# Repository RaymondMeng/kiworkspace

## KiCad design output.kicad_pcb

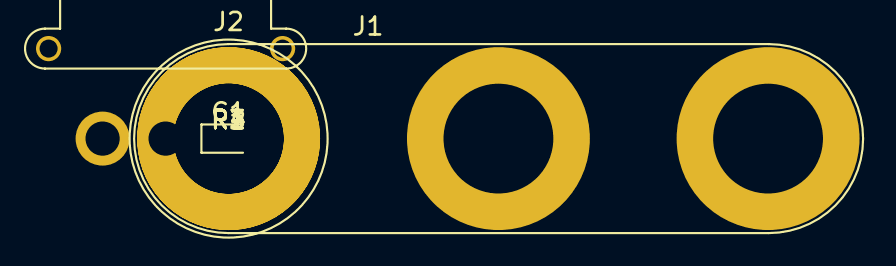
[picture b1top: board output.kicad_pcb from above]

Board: 2 copper layers, 8 parts (0 on the bottom side), 6 nets, no tracks yet.

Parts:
C1: 1uf; CP_EIA-1608-10_AVX-L
J1: Conn_01x03; Banana_Jack_3Pin
J2: Conn_01x01; Banana_Jack_1Pin
Q1: PNP; AMASS_MR30PW-FB_1x03_P3.50mm_Horizontal
R1: 10R; R_0201_0603Metric
R2: 10K; R_0201_0603Metric
R3: 1K; R_0201_0603Metric
R4: 5R; R_0201_0603Metric

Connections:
/out: J2.1, R2.1
/signal: C1.2, J1.1
GND: J1.2, Q1.3 (E), R1.2
unnamed: C1.1, Q1.2 (B), R1.1, R4.2
unnamed: Q1.1 (C), R2.2, R3.2
VCC: J1.3, R3.1, R4.1

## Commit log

2023-11-01 finish parsing of netlist's net
2023-11-02 finish basic barsing of net
2023-11-03 first_version
2023-11-03 fix some error
2023-11-04 #2 fix error: 替换正则模式为首尾匹配，解决fp_name部分缺失问题
2023-11-04 #3 fix error: 修复reference_name没有独立命名的问题
2023-11-05 #4 add & fix: 增加了pad的net内容，修复了若干问题
2023-11-05 #5 fix error: 修复net网络匹配错误
2023-11-06 #6 add: 增加了pcbnew布局布线设置
2023-12-15 Create LICENSE
